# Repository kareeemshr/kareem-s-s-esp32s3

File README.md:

**quick warning, the traces for the 5volt regulator are too small for what it's max output is. I also apologize for it having too many layers since I'm not exactly the best at routing(I suck at it alot) I used more layers than necessary :(**

this is supposed to be a personal devboard using the esp32s,it has LED's in the shape of a heart,two cap touch plates and a buzzer.

**the led's are connected to io 48**

**the buzzer is connected to io 16**

**the cap touch plates are connected to io 4 and 8**

this doesnt have to be built with pcba but i **STRONGLY** recommend it cus i didint design it with hand soldering in mind because i personally cant get sorurce all the parts on the board on my own without paying outrageous prices for shipping so pcba is cheaper for me
heres the schem:

heres the pcb:

heres a 3d model:

heres my zineeee page:

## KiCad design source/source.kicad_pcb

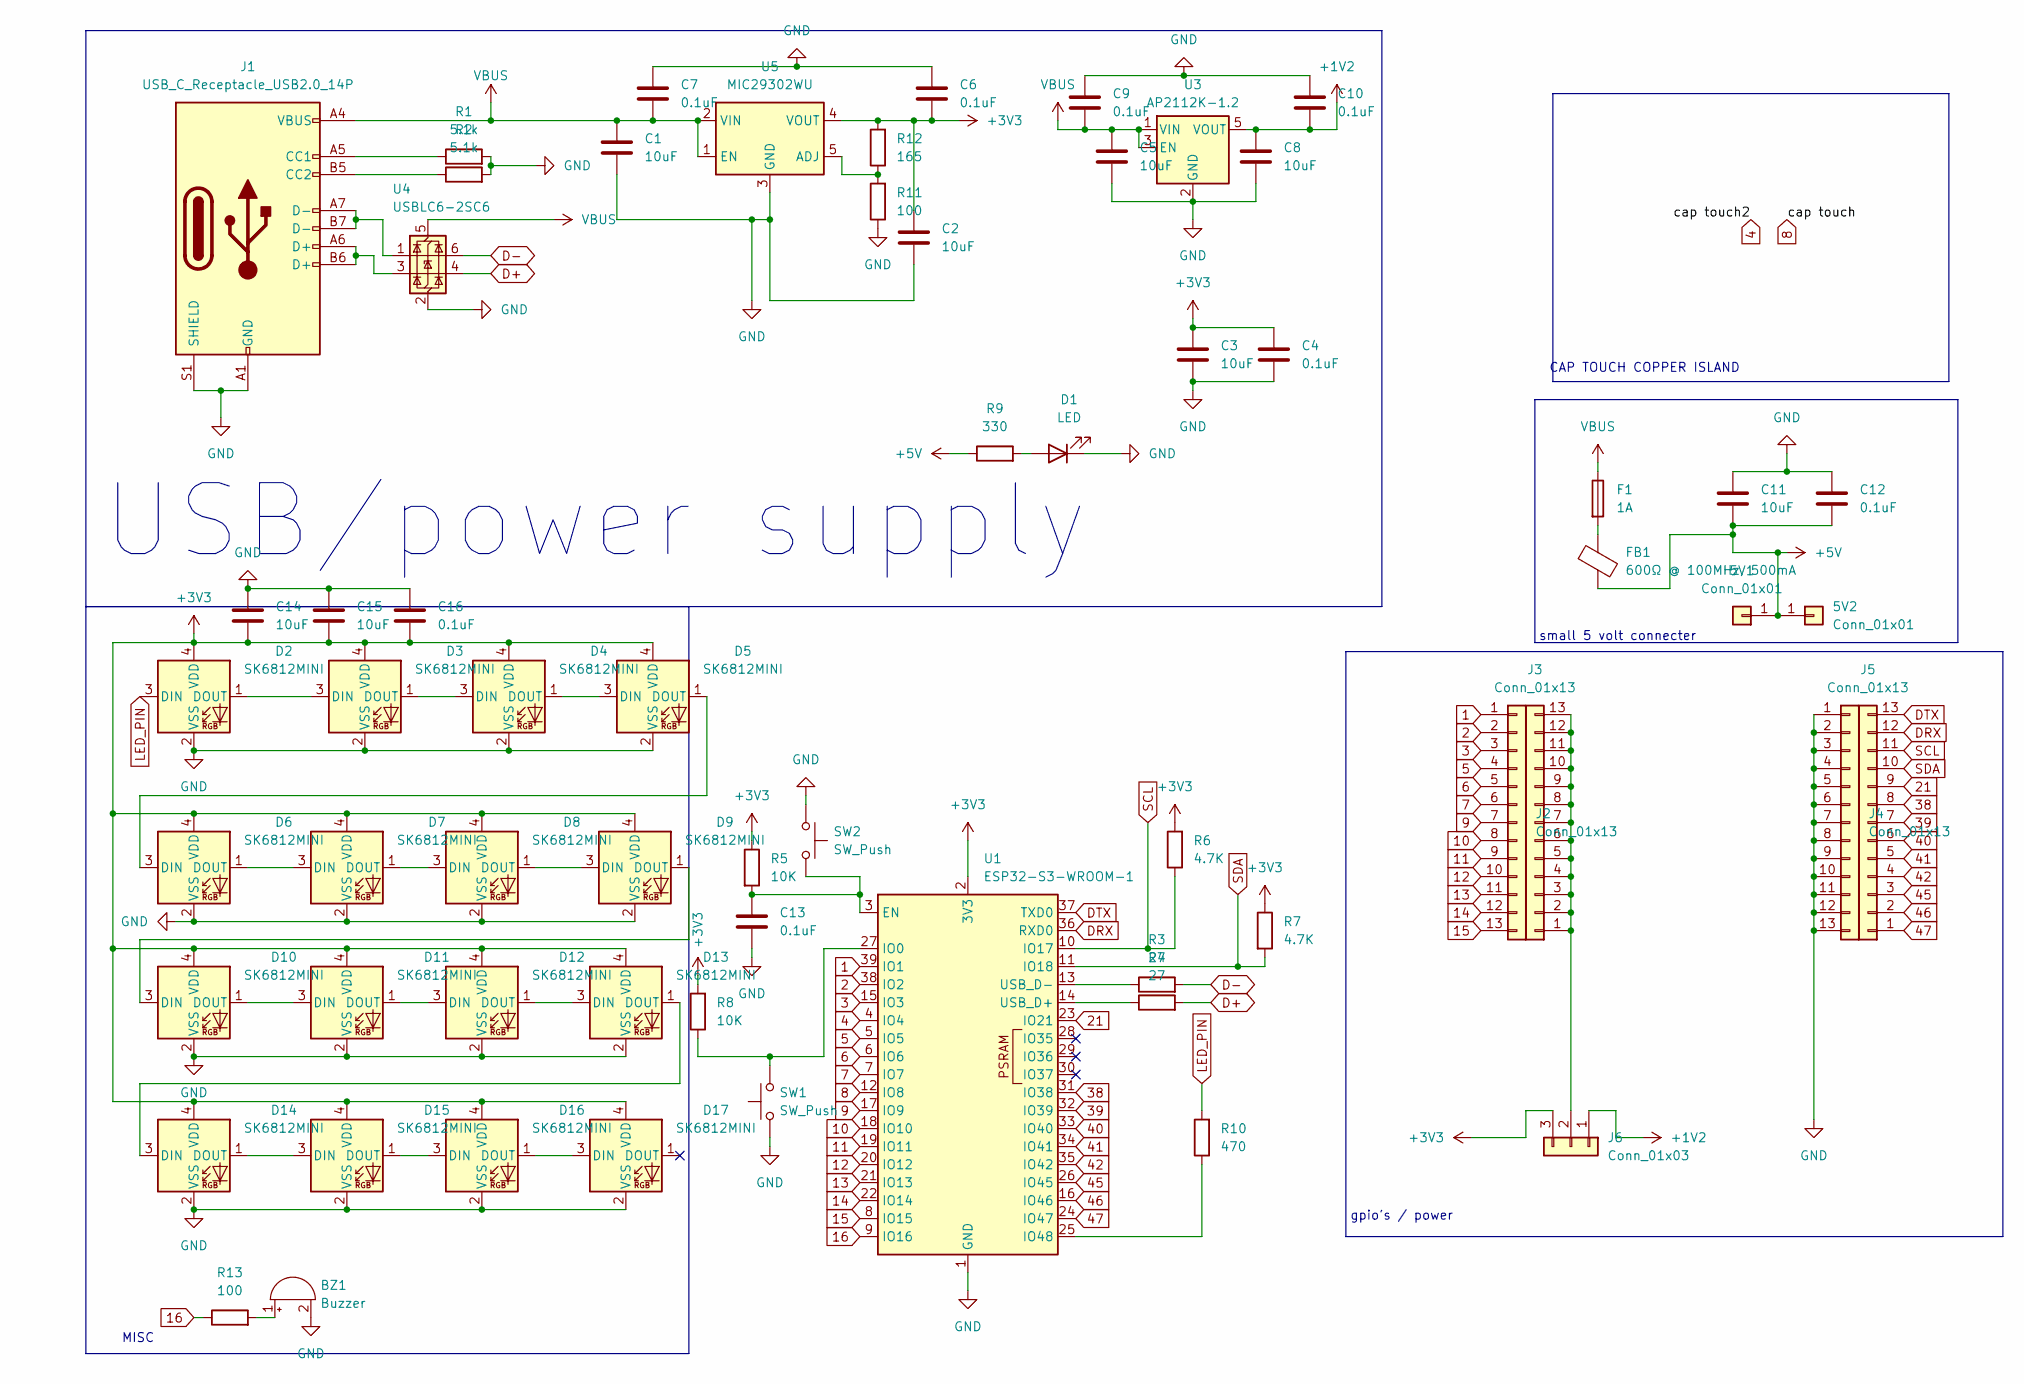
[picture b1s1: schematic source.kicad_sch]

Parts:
5V1, 5V2: Conn_01x01; PinHeader_1x01_P2.54mm_Vertical
BZ1: Buzzer; Buzzer_12x9.5RM7.6
C1, C2, C3, C5, C8, C11, C14, C15: 10uF; C_0402_1005Metric
C4, C6, C7, C9, C10, C12, C13, C16: 0.1uF; C_0402_1005Metric
D1: LED; LED_0402_1005Metric
D2, D3, D4, D5, D6, D7, D8, D9, D10, D11, D12, D13, D14, D15, D16, D17: SK6812MINI; LED_SK6812MINI_PLCC4_3.5x3.5mm_P1.75mm
F1: 1A; Fuse_0603_1608Metric
FB1: 600Ω @ 100MHz, 500mA; L_0805_2012Metric
J1: USB_C_Receptacle_USB2.0_14P; USB_C_Receptacle_HRO_TYPE-C-31-M-12
J2, J3, J4, J5: Conn_01x13; PinHeader_1x13_P2.54mm_Vertical
J6: Conn_01x03; PinHeader_1x03_P2.54mm_Vertical
R1, R2: 5.1k; R_0402_1005Metric
R3, R4: 27; R_0402_1005Metric
R5, R8: 10K; R_0402_1005Metric
R6, R7: 4.7K; R_0402_1005Metric
R9: 330; R_0402_1005Metric
R10: 470; R_0402_1005Metric
R11, R13: 100; R_0402_1005Metric
R12: 165; R_0402_1005Metric
SW1, SW2: SW_Push; SW_Push_SPST_NO_Alps_SKRK
U1: ESP32-S3-WROOM-1
U3: AP2112K-1.2; SOT-23-5
U4: USBLC6-2SC6; SOT-23-6
U5: MIC29302WU; TO-263-5_TabPin3

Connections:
1: J2.1, U1.39 (IO1)
2: J2.2, U1.38 (IO2)
3: J2.3, U1.15 (IO3)
4: U1.4 (IO4)
5: J2.4, U1.5 (IO5)
6: J2.5, U1.6 (IO6)
7: J2.6, U1.7 (IO7)
8: U1.12 (IO8)
9: J2.7, U1.17 (IO9)
10: J2.8, U1.18 (IO10)
11: J2.9, U1.19 (IO11)
12: J2.10, U1.20 (IO12)
13: J2.11, U1.21 (IO13)
14: J2.12, U1.22 (IO14)
15: J2.13, U1.8 (IO15)
16: R13.1, U1.9 (IO16)
21: J5.9, U1.23 (IO21)
38: J5.8, U1.31 (IO38)
39: J5.7, U1.32 (IO39)
40: J5.6, U1.33 (IO40)
41: J5.5, U1.34 (IO41)
42: J5.4, U1.35 (IO42)
45: J5.3, U1.26 (IO45)
46: J5.2, U1.16 (IO46)
47: J5.1, U1.24 (IO47)
+1V2: C8.1, C10.2, J6.1, U3.5 (VOUT)
+3V3: C2.1, C3.1, C4.1, C6.2, C14.1, C15.1, C16.1, D2.4 (VDD), D3.4 (VDD), D4.4 (VDD), D5.4 (VDD), D6.4 (VDD), D7.4 (VDD), D8.4 (VDD), D9.4 (VDD), D10.4 (VDD), D11.4 (VDD), D12.4 (VDD), D13.4 (VDD), D14.4 (VDD), D15.4 (VDD), D16.4 (VDD), D17.4 (VDD), J6.3, R5.1, R6.2, R7.1, R8.2, R12.2, U1.2 (3V3), U5.4 (VOUT)
+5V: 5V1.1, 5V2.1, C11.2, C12.2, FB1.2, R9.1
D+: R4.2, U4.4 (I/O2)
D-: R3.2, U4.6 (I/O1)
DRX: J5.12, U1.36 (RXD0)
DTX: J5.13, U1.37 (TXD0)
GND: BZ1.2 (-), C1.2, C2.2, C3.2, C4.2, C5.2, C6.1, C7.1, C8.2, C9.1, C10.1, C11.1, C12.1, C13.2, C14.2, C15.2, C16.2, D1.1 (K), D2.2 (VSS), D3.2 (VSS), D4.2 (VSS), D5.2 (VSS), D6.2 (VSS), D7.2 (VSS), D8.2 (VSS), D9.2 (VSS), D10.2 (VSS), D11.2 (VSS), D12.2 (VSS), D13.2 (VSS), D14.2 (VSS), D15.2 (VSS), D16.2 (VSS), D17.2 (VSS), J1.A1 (GND), J1.A12 (GND), J1.B1 (GND), J1.B12 (GND), J1.S1 (SHIELD), J4.1, J4.2, J4.3, J4.4, J4.5, J4.6, J4.7, J4.8, J4.9, J4.10, J4.11, J4.12, J4.13, R1.2, R2.2, R11.1, SW1.1, SW2.1, U1.1 (GND), U1.40 (GND), U1.41 (GND), U3.2 (GND), U4.2 (GND), U5.3 (GND); also elsewhere on the board
LED_PIN: D2.3 (DIN), R10.2
unnamed: BZ1.1 (+), R13.2
unnamed: D1.2 (A), R9.2
unnamed: D2.1 (DOUT), D3.3 (DIN)
unnamed: D3.1 (DOUT), D4.3 (DIN)
unnamed: D4.1 (DOUT), D5.3 (DIN)
unnamed: D5.1 (DOUT), D6.3 (DIN)
unnamed: D6.1 (DOUT), D7.3 (DIN)
unnamed: D7.1 (DOUT), D8.3 (DIN)
unnamed: D8.1 (DOUT), D9.3 (DIN)
unnamed: D9.1 (DOUT), D10.3 (DIN)
unnamed: D10.1 (DOUT), D11.3 (DIN)
unnamed: D11.1 (DOUT), D12.3 (DIN)
unnamed: D12.1 (DOUT), D13.3 (DIN)
unnamed: D13.1 (DOUT), D14.3 (DIN)
unnamed: D14.1 (DOUT), D15.3 (DIN)
unnamed: D15.1 (DOUT), D16.3 (DIN)
unnamed: D16.1 (DOUT), D17.3 (DIN)
unnamed: F1.2, FB1.1
unnamed: J1.A5 (CC1), R1.1
unnamed: J1.B5 (CC2), R2.1
unnamed: J1.A6 (D+), J1.B6 (D+), U4.3 (I/O2)
unnamed: J1.A7 (D-), J1.B7 (D-), U4.1 (I/O1)
unnamed: J3.1, J3.2, J3.3, J3.4, J3.5, J3.6, J3.7, J3.8, J3.9, J3.10, J3.11, J3.12, J3.13, J6.2
unnamed 57: C13.1, R5.2, SW2.2, U1.3 (EN); also elsewhere on the board
unnamed 58: R8.1, SW1.2, U1.27 (IO0); also elsewhere on the board
unnamed: R10.1, U1.25 (IO48)
unnamed: R4.1, U1.14 (USB_D+)
unnamed: R3.1, U1.13 (USB_D-)
unnamed: R11.2, R12.1, U5.5 (ADJ)
SCL: J5.11, R6.1, U1.10 (IO17)
SDA: J5.10, R7.2, U1.11 (IO18)
VBUS: C1.1, C5.1, C7.2, C9.2, F1.1, J1.A4 (VBUS), J1.A9 (VBUS), J1.B4 (VBUS), J1.B9 (VBUS), U3.1 (VIN), U3.3 (EN), U4.5 (VBUS), U5.1 (EN), U5.2 (VIN)

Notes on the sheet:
MISC
gpio's / power
CAP TOUCH COPPER ISLAND
small 5 volt connecter
USB/power supply

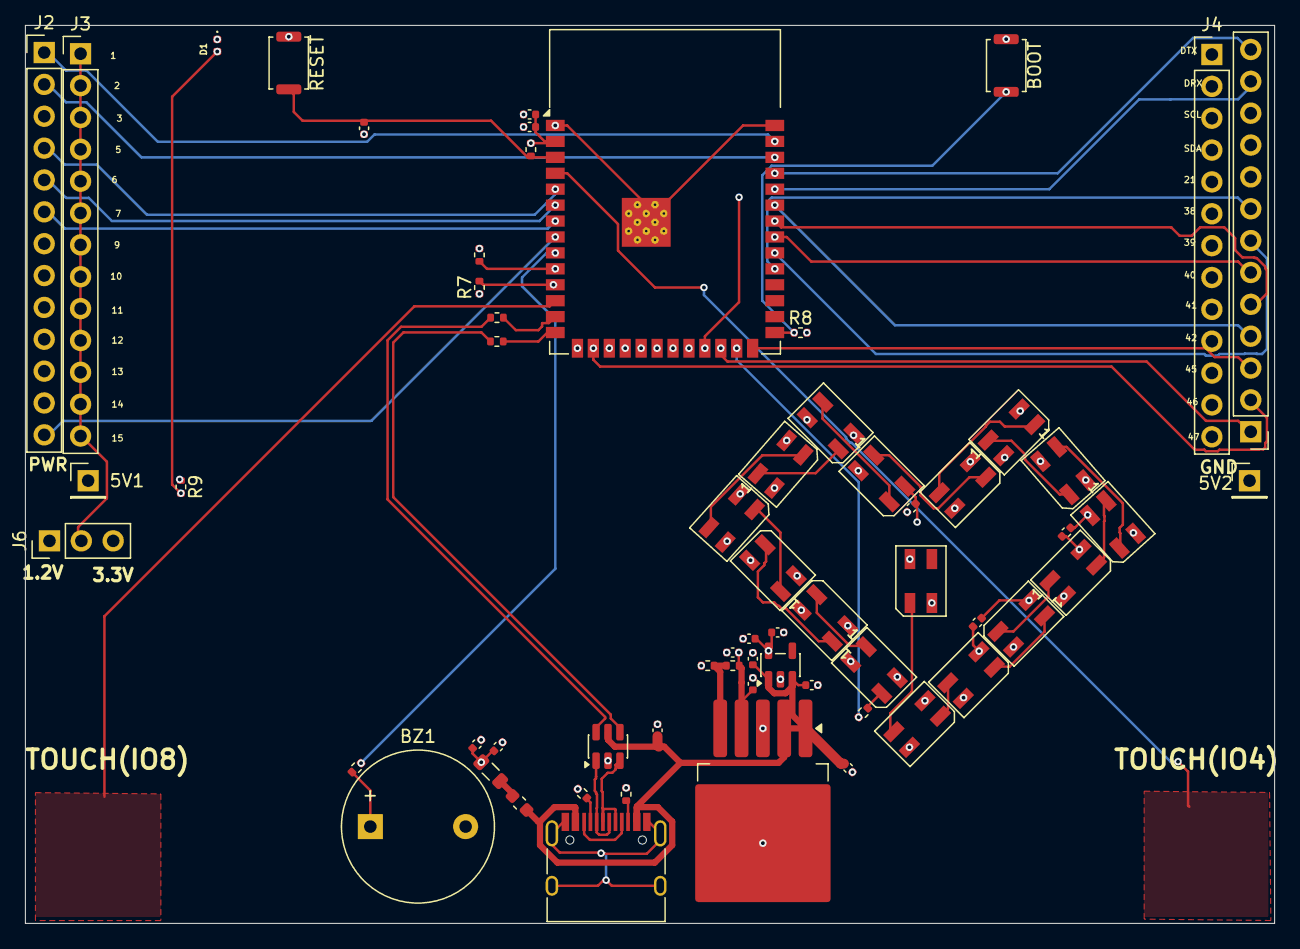
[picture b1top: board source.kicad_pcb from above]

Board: 4 copper layers, 99.6 x 71.6 mm, 63 parts (0 on the bottom side), 64 nets.

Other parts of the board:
BOOT: SW_Push; SW_Push_SPST_NO_Alps_SKRK
RESET: SW_Push; SW_Push_SPST_NO_Alps_SKRK

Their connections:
GND: BOOT.1, RESET.1; also elsewhere on the board
unnamed 57: RESET.2; also elsewhere on the board
unnamed 58: BOOT.2; also elsewhere on the board

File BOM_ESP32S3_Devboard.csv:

Designator,Footprint,Quantity,Value,LCSC Part #,Description,Price ~(USD)
"5V1, 5V2",PinHeader_1x01_P2.54mm_Vertical,2,Conn_01x01,C2337072,1-pin 2.54mm pin header,~0.01
"BOOT, RESET",SW_Push_SPST_NO_Alps_SKRK,2,SW_Push,C318884,6x6mm SMD tactile switch TS-1187A,~0.05
BUZZER,Buzzer_12x9.5RM7.6,1,Buzzer,C96093,Passive buzzer 12mm TMB12A05,~0.30
"C1, C11, C14, C15, C2, C3, C5, C8",0402,8,10uF,C15525,10uF 10V X5R 0402 MLCC,~0.02
"C10, C12, C13, C16, C4, C6, C7, C9",0402,8,0.1uF,C307331,100nF 50V X7R 0402 MLCC,~0.01
D1,0402,1,LED,C2286,Red LED 0402 20mA,~0.02
"D2, D3, D4, D5, D6, D7, D8, D9, D10, D11, D12, D13, D14, D15, D16, D17",LED_SK6812MINI_PLCC4_3.5x3.5mm_P1.75mm,16,SK6812MINI,C2909059,SK6812MINI RGB addressable LED 3.3V,~0.15
F1,0603,1,1A,C369154,1A polyfuse resettable 0603,~0.10
FB1,0805,1,"600Ω @ 100MHz, 500mA",C1015573,Ferrite bead 600R 100MHz 500mA 0805,~0.05
J1,USB_C_Receptacle_HRO_TYPE-C-31-M-12,1,USB_C_Receptacle_USB2.0_14P,C165948,USB-C 2.0 14-pin SMD receptacle HRO TYPE-C-31-M-12,~0.50
"J2, J3",PinHeader_2x13_P2.54mm_Vertical,2,Conn_02x13_Odd_Even,C2690452,2x13 2.54mm dual row pin header,~0.20
JP1,PinHeader_1x03_P2.54mm_Vertical,1,Jumper_3_Bridged12,C2337072,1x3 2.54mm pin header (power switching jumper),~0.05
"R1, R2",0402,2,5.1k,C25905,5.1kΩ 1% 0402 CC1/CC2 pull-down,~0.01
R10,0402,1,470,C25117,470Ω 1% 0402 NeoPixel data resistor,~0.01
"R11, R13",0402,2,100,C25076,100Ω 1% 0402 ADJ divider bottom,~0.01
R12,0402,1,165,C25083,165Ω 1% 0402 ADJ divider top (use 162Ω if unavailable),~0.01
"R3, R4",0402,2,27,C25100,27Ω 1% 0402 USB D+/D- series resistors,~0.01
"R5, R8",0402,2,10K,C25744,10kΩ 1% 0402 EN and IO0 pull-up,~0.01
"R6, R7",0402,2,4.7K,C25900,4.7kΩ 1% 0402 I2C SDA/SCL pull-up,~0.01
R9,0402,1,330,C25104,330Ω 1% 0402 power LED,~0.01
U1,ESP32-S3-WROOM-1,1,ESP32-S3-WROOM-1,C2913202,ESP32-S3-WROOM-1 WiFi+BT module 4MB flash,~3.50
U3,SOT-23-5,1,AP2112K-1.2,C88099,AP2112K-1.2 600mA LDO 1.2V SOT-23-5,~0.15
U4,SOT-23-6,1,USBLC6-2SC6,C7519,USBLC6-2SC6 USB ESD protection SOT-23-6,~0.10
U5,TO-263-5_TabPin3,1,MIC29302WU,C914662,MIC29302WU adjustable LDO 3A TO-263-5,~1.20

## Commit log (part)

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2026-03-29 Update README with project details and connections
    Added project description and connection details for components.
2026-03-29 Update README with PCB and 3D model images
    Added images of the PCB and 3D model to the README.
2026-03-30 Update BOM with new part numbers and descriptions
2026-04-02 Add zine page image to README
2026-04-02 Recommend PCBA for easier sourcing of components
    Added recommendation for PCBA due to sourcing issues.
2026-04-02 Add component links to bom.csv
    Added links to components in BOM for easy access.
2026-04-02 Update BOM entries in bom.csv
    Replaced the existing BOM data with updated entries.
